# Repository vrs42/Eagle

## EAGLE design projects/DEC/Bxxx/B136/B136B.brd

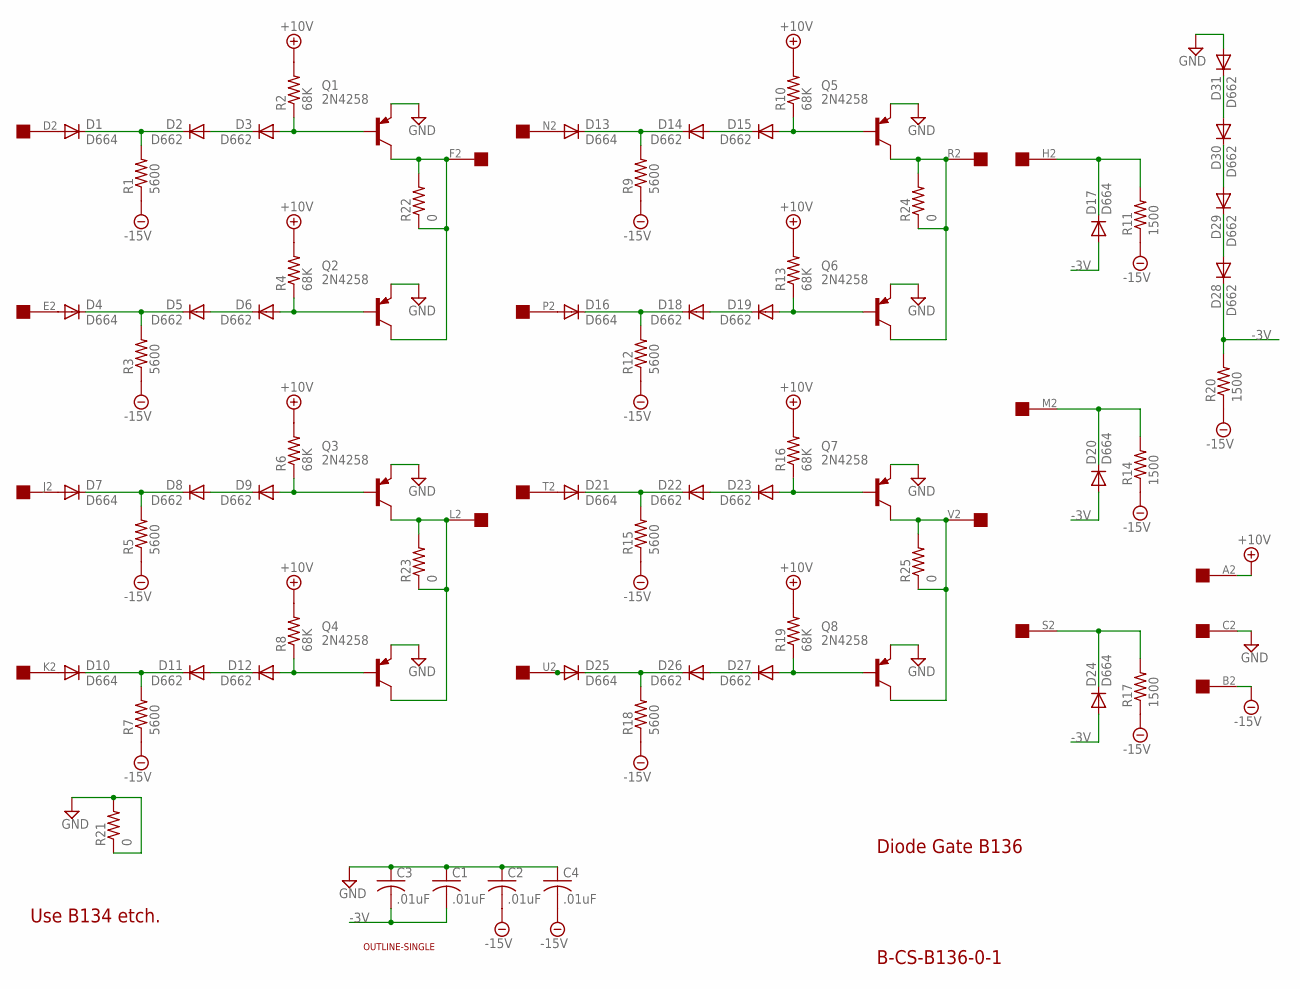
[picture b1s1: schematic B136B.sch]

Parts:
C1, C2, C3, C4: .01uF; C063-025X075
D1, D4, D7, D10, D13, D16, D17, D20, D21, D24, D25: D664; DO35-10
D2, D3, D5, D6, D8, D9, D11, D12, D14, D15, D18, D19, D22, D23, D26, D27, D28, D29, D30, D31: D662; DO35-10
Q1, Q2, Q3, Q4, Q5, Q6, Q7, Q8: 2N4258; TO5
R1, R3, R5, R7, R9, R12, R15, R18: 5600; 0207/10
R2, R4, R6, R8, R10, R13, R16, R19: 68K; 0207/10
R11, R14, R17, R20: 1500; 0207/10
R21, R22, R23, R24, R25: 0; 0207/10
U$1: OUTLINE-SINGLE; SINGLE
U$2: EDGE-1; EDGE-CON1

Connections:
+10V: R2.2, R4.2, R6.2, R8.2, R10.2, R13.2, R16.2, R19.2, U$2.A2
-3V: C1.2, C3.2, D17.A, D20.A, D24.A, D28.C, R20.2
-15V: C2.2, C4.2, R1.1, R3.1, R5.1, R7.1, R9.1, R11.1, R12.1, R14.1, R15.1, R17.1, R18.1, R20.1, U$2.B2
GND: C1.1, C2.1, C3.1, C4.1, D31.A, Q1.1 (E), Q2.1 (E), Q3.1 (E), Q4.1 (E), Q5.1 (E), Q6.1 (E), Q7.1 (E), Q8.1 (E), R21.1, R21.2, U$2.C2
unnamed: D4.C, D5.C, R3.2
unnamed: D10.C, D11.C, R7.2
unnamed: D3.A, Q1.2 (B), R2.1
unnamed: D13.C, D14.C, R9.2
unnamed: D1.C, D2.C, R1.2
unnamed: D4.A, U$2.E2
unnamed: D13.A, U$2.N2
unnamed: D11.A, D12.C
unnamed: D5.A, D6.C
unnamed: D1.A, U$2.D2
unnamed: D14.A, D15.C
unnamed: D6.A, Q2.2 (B), R4.1
unnamed: Q1.3 (C), Q2.3 (C), R22.1, R22.2, U$2.F2
unnamed: D7.C, D8.C, R5.2
unnamed: D2.A, D3.C
unnamed: D7.A, U$2.J2
unnamed: D17.C, R11.2, U$2.H2
unnamed: D15.A, Q5.2 (B), R10.1
unnamed: D10.A, U$2.K2
unnamed: D20.C, R14.2, U$2.M2
unnamed: D8.A, D9.C
unnamed: D9.A, Q3.2 (B), R6.1
unnamed: D16.C, D18.C, R12.2
unnamed: D12.A, Q4.2 (B), R8.1
unnamed: D24.C, R17.2, U$2.S2
unnamed: D30.A, D31.C
unnamed: D29.A, D30.C
unnamed: D19.A, Q6.2 (B), R13.1
unnamed: D28.A, D29.C
unnamed: D18.A, D19.C
unnamed: D23.A, Q7.2 (B), R16.1
unnamed: D21.C, D22.C, R15.2
unnamed: D22.A, D23.C
unnamed: D27.A, Q8.2 (B), R19.1
unnamed: D16.A, U$2.P2
unnamed: D21.A, U$2.T2
unnamed: D25.C, D26.C, R18.2
unnamed: D26.A, D27.C
unnamed: Q7.3 (C), Q8.3 (C), R25.1, R25.2, U$2.V2
unnamed: D25.A, U$2.U2
unnamed: Q3.3 (C), Q4.3 (C), R23.1, R23.2, U$2.L2
unnamed: Q5.3 (C), Q6.3 (C), R24.1, R24.2, U$2.R2

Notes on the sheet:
Diode Gate B136
B-CS-B136-0-1
Use B134 etch.

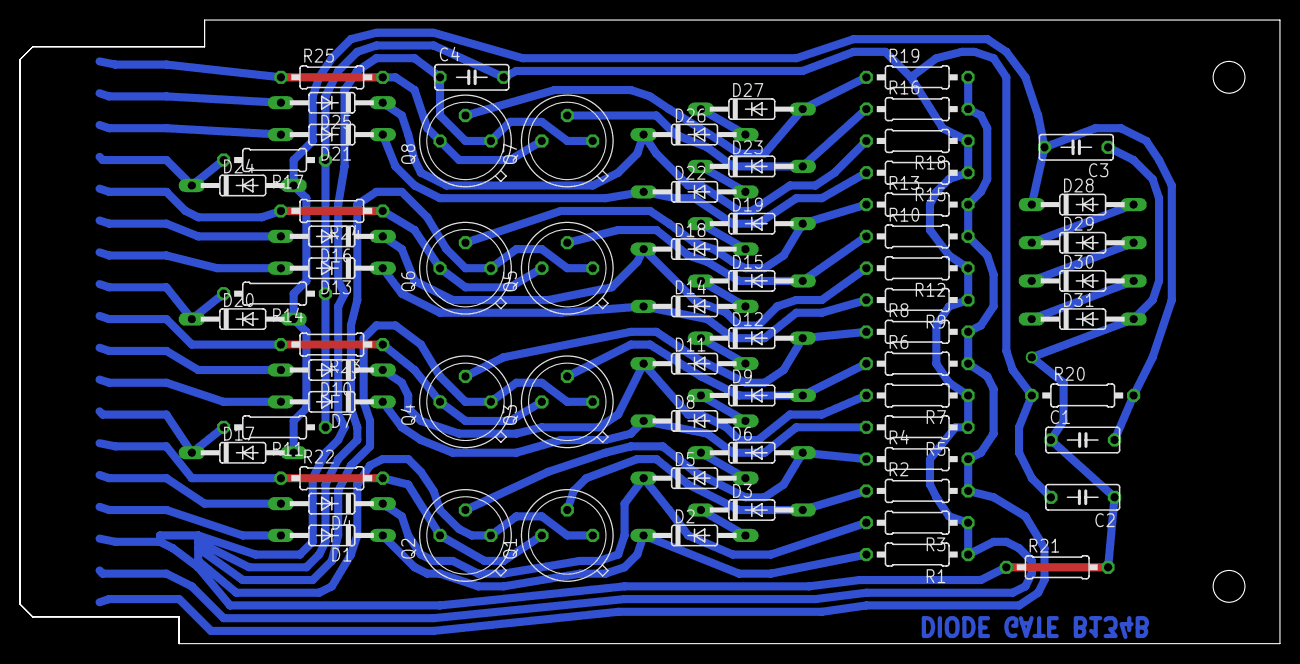
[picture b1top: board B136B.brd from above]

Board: 2 copper layers, 125.7 x 62.2 mm, 70 parts (0 on the bottom side), 46 nets.

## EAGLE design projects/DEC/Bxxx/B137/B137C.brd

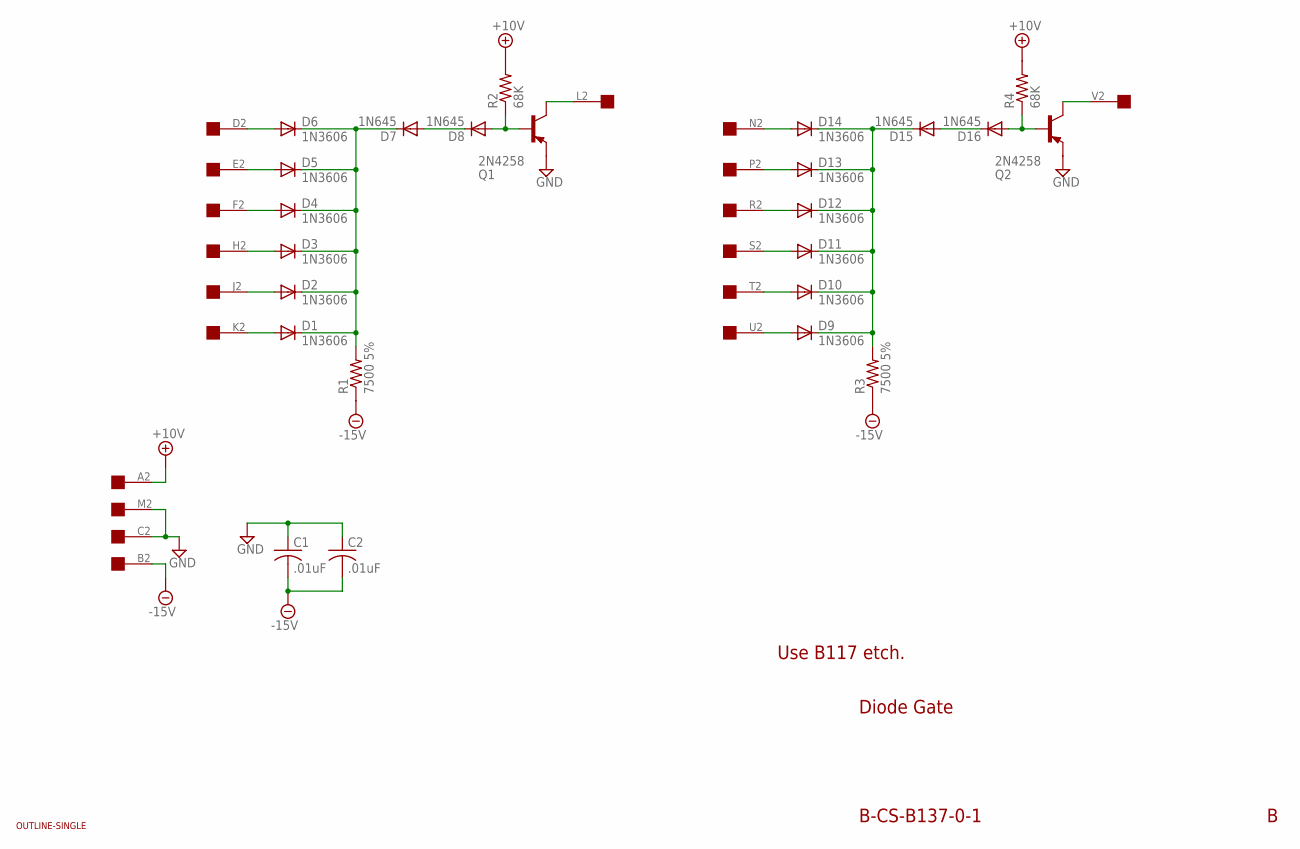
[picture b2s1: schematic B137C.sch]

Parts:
C1, C2: .01uF; C050-025X075
D1, D2, D3, D4, D5, D6, D9, D10, D11, D12, D13, D14: 1N3606; DO35-10
D7, D8, D15, D16: 1N645; DO35-10
Q1, Q2: 2N4258; TO5
R1, R3: 7500 5%; 0207/10
R2, R4: 68K; 0207/10
U$1: OUTLINE-SINGLE; SINGLE
U$2: EDGE-1; EDGE-CON1

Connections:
+10V: R2.2, R4.2, U$2.A2
-15V: C1.2, C2.2, R1.1, R3.1, U$2.B2
D: D6.A, U$2.D2
E: D5.A, U$2.E2
F: D4.A, U$2.F2
GND: C1.1, C2.1, Q1.1 (E), Q2.1 (E), U$2.C2, U$2.M2
H: D3.A, U$2.H2
J: D2.A, U$2.J2
K: D1.A, U$2.K2
L: Q1.3 (C), U$2.L2
N: D14.A, U$2.N2
unnamed: D1.C, D2.C, D3.C, D4.C, D5.C, D6.C, D7.C, R1.2
unnamed: D7.A, D8.C
unnamed: D8.A, Q1.2 (B), R2.1
unnamed: D9.C, D10.C, D11.C, D12.C, D13.C, D14.C, D15.C, R3.2
unnamed: D15.A, D16.C
unnamed: D16.A, Q2.2 (B), R4.1
P: D13.A, U$2.P2
R: D12.A, U$2.R2
S: D11.A, U$2.S2
T: D10.A, U$2.T2
U: D9.A, U$2.U2
V: Q2.3 (C), U$2.V2

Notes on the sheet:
Diode Gate
B-CS-B137-0-1
Use B117 etch.

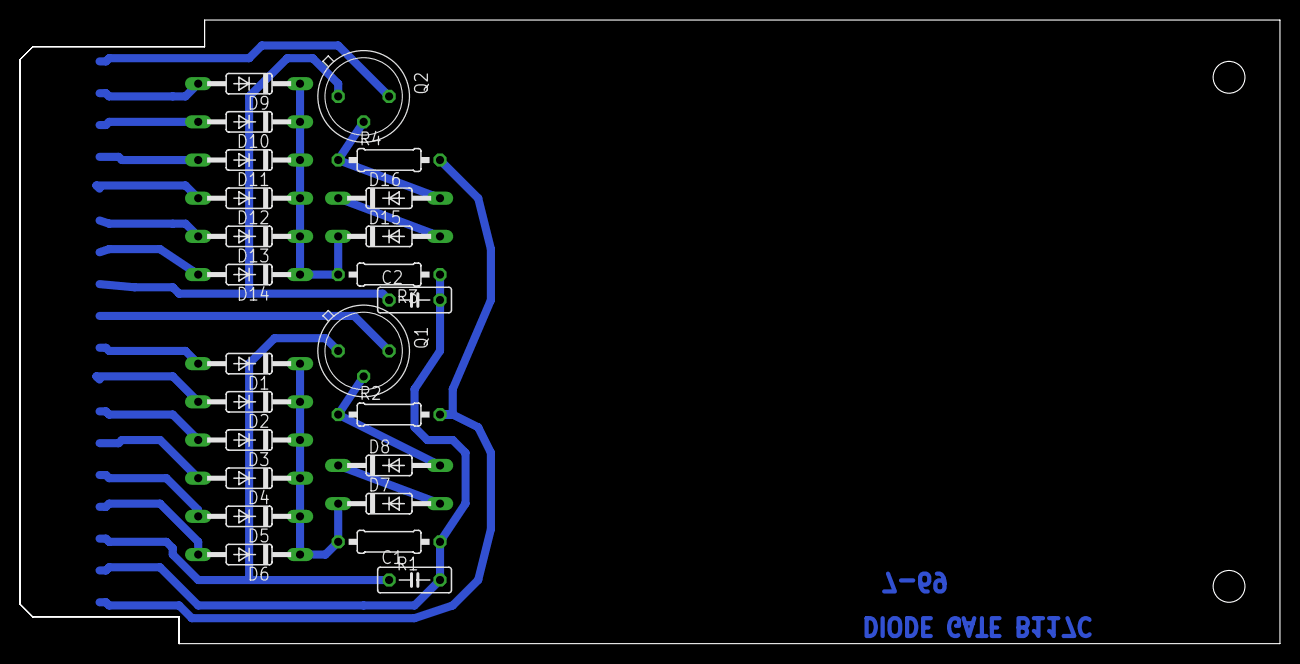
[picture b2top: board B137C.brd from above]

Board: 2 copper layers, 125.7 x 62.2 mm, 26 parts (0 on the bottom side), 23 nets.

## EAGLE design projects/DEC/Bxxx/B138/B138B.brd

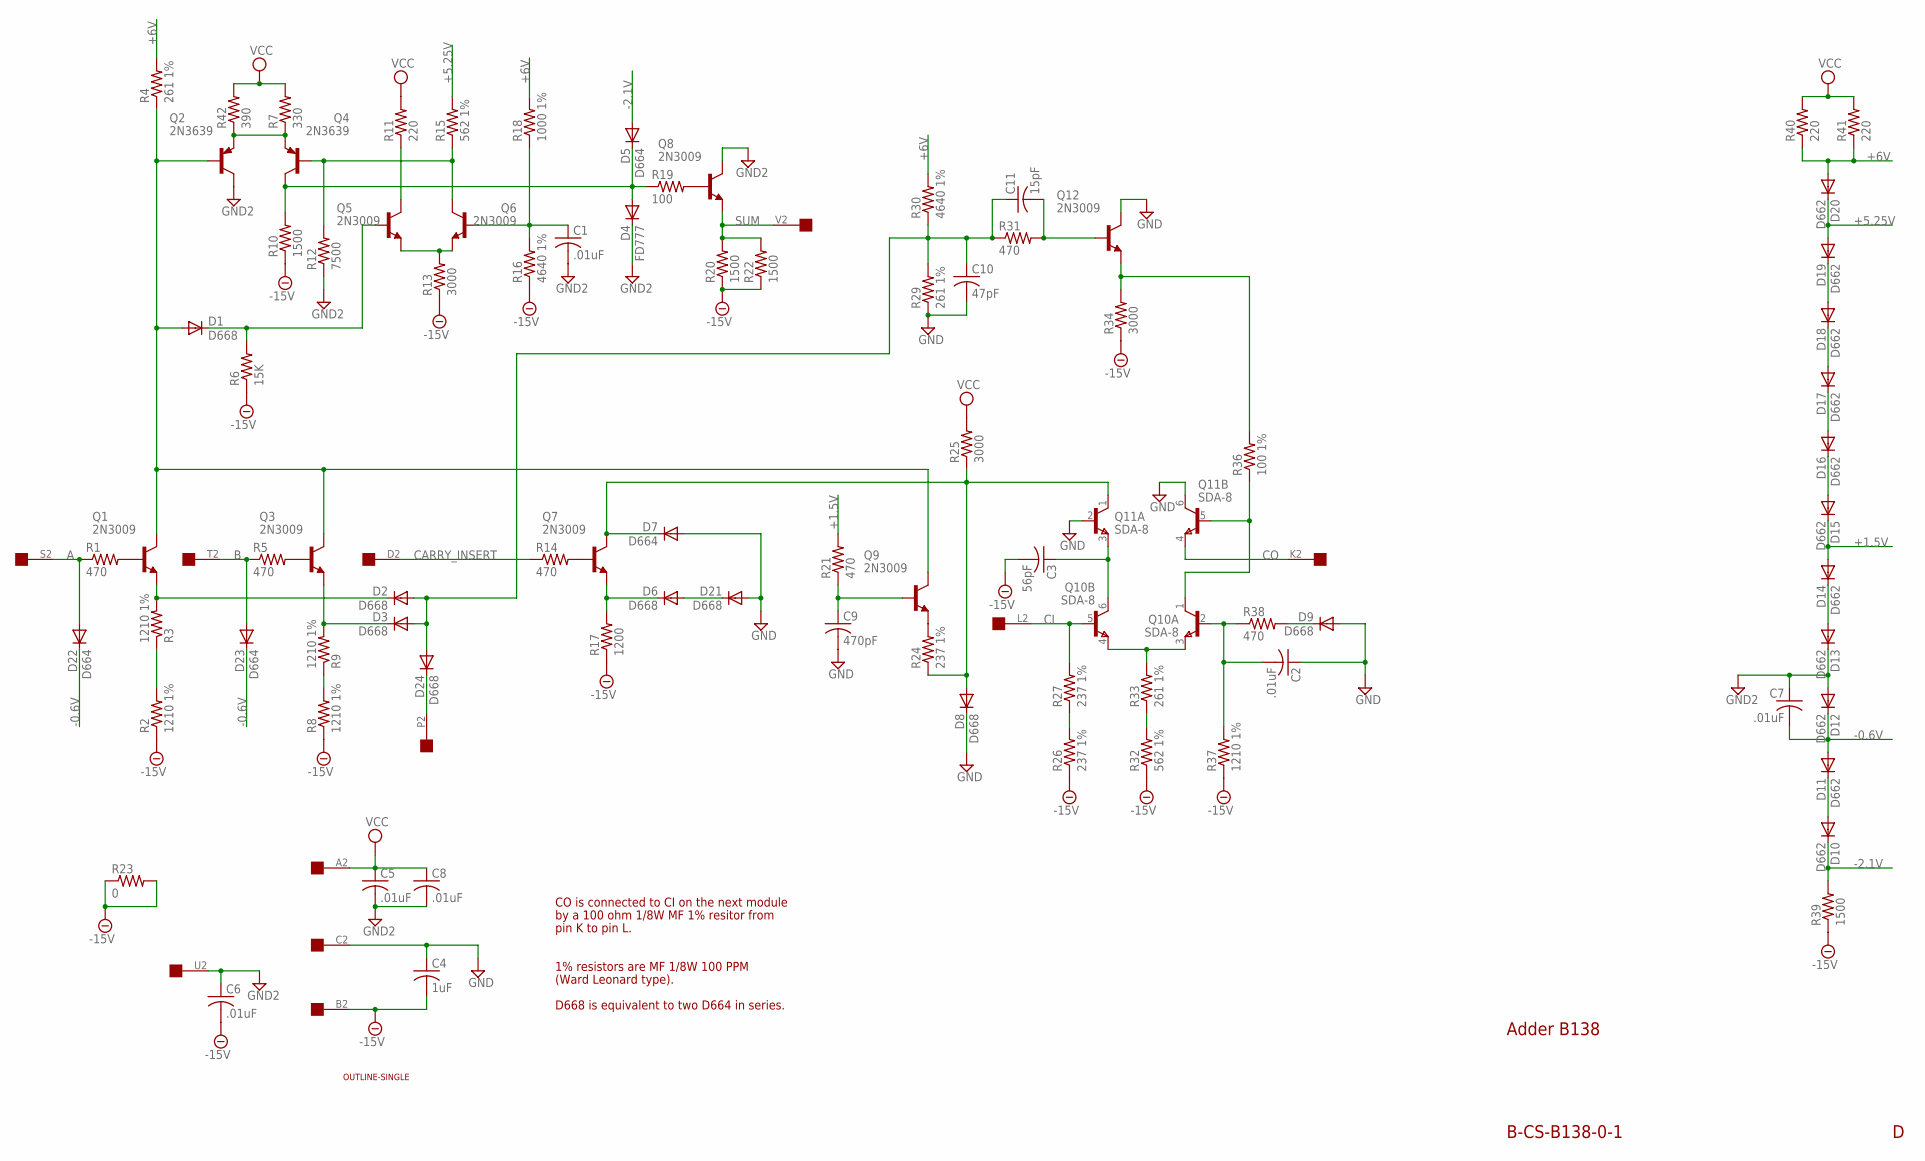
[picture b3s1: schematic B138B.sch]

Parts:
C1, C2, C5, C6, C7, C8: .01uF; C063-025X075
C3: 56pF; C063-025X075
C4: 1uF; C102-043X133
C9: 470pF; C063-025X075
C10: 47pF; C063-025X075
C11: 15pF; C063-025X075
D1, D2, D3, D6, D8, D9, D21, D24: D668; DO35-10
D4: FD777; DO35-10
D5, D7, D22, D23: D664; DO35-10
D10, D11, D12, D13, D14, D15, D16, D17, D18, D19, D20: D662; DO35-10
Q1, Q3, Q5, Q6, Q7, Q8, Q9, Q12: 2N3009; TO5
Q2, Q4: 2N3639; TO5
Q10, Q11: SDA-8; TO78
R1, R5, R14, R21, R31, R38: 470; 0207/10
R2, R3, R8, R9, R37: 1210 1%; 0207/15
R4, R29, R33: 261 1%; 0207/15
R6: 15K; 0207/10
R7: 330; 0207/10
R10, R20, R22, R39: 1500; 0207/10
R11, R40, R41: 220; 0207/10
R12: 7500; 0207/10
R13, R25, R34: 3000; 0207/10
R15, R32: 562 1%; 0207/15
R16, R30: 4640 1%; 0207/15
R17: 1200; 0207/10
R18: 1000 1%; 0207/15
R19: 100; 0207/10
R23: 0; 0207/10
R24, R26, R27: 237 1%; 0207/15
R36: 100 1%; 0207/15
R42: 390; 0207/10
U$1: OUTLINE-SINGLE; SINGLE
U$2: EDGE-1; EDGE-CON1

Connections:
+1.5V: D14.A, D15.C, R21.2
+5.25V: D19.A, D20.C, R15.2
+6V: D20.A, R4.2, R18.2, R30.2, R40.1, R41.1
-0.6V: C7.2, D11.A, D12.C, D22.C, D23.C
-2.1V: D5.A, D10.C, R39.2
-15V: C3.2, C4.2, C6.2, R2.1, R6.1, R8.1, R10.1, R13.1, R16.1, R17.1, R20.1, R22.1, R23.1, R23.2, R26.1, R32.1, R34.1, R37.1, R39.1, U$2.B2
A: D22.A, R1.1, U$2.S2
B: D23.A, R5.1, U$2.T2
CARRY_INSERT: R14.1, U$2.D2
CI: Q10.5 (B), R27.2, U$2.L2
CO: Q11.4 (E), U$2.K2
GND: C2.1, C4.1, C9.2, C10.2, D7.A, D8.C, D9.A, D21.A, Q11.2 (B), Q11.6 (C), Q12.3 (C), R29.1, U$2.C2
GND2: C1.2, C5.2, C6.1, C7.1, C8.2, D4.C, D12.A, D13.C, Q2.3 (C), Q8.3 (C), R12.1, U$2.U2
unnamed: D1.A, Q1.3 (C), Q2.2 (B), Q3.3 (C), Q9.3 (C), R4.1
unnamed: D2.C, Q1.1 (E), R3.2
unnamed: R2.2, R3.1
unnamed: D3.C, Q3.1 (E), R9.2
unnamed: R8.2, R9.1
unnamed: Q1.2 (B), R1.2
unnamed: Q3.2 (B), R5.2
unnamed: D24.C, U$2.P2
unnamed: C10.1, C11.1, D2.A, D3.A, D24.A, R29.2, R30.1, R31.1
unnamed: D6.C, Q7.1 (E), R17.2
unnamed: Q7.2 (B), R14.2
unnamed: D6.A, D21.C
unnamed: D7.C, D8.A, Q7.3 (C), Q11.1 (C), R24.1, R25.1
unnamed: Q9.1 (E), R24.2
unnamed: C9.1, Q9.2 (B), R21.1
unnamed: Q10.3 (E), Q10.4 (E), R33.2
unnamed: R32.2, R33.1
unnamed: D17.A, D18.C
unnamed: D18.A, D19.C
unnamed: C3.1, Q10.6 (C), Q11.3 (E)
unnamed: D15.A, D16.C
unnamed: D16.A, D17.C
unnamed: D13.A, D14.C
unnamed: Q10.1 (C), Q11.5 (B), R36.1
unnamed: R26.2, R27.1
unnamed: D10.A, D11.C
unnamed: C2.2, Q10.2 (B), R37.2, R38.1
unnamed: D9.C, R38.2
unnamed: Q2.1 (E), Q4.1 (E), R7.1, R42.1
unnamed: C1.1, Q6.2 (B), R16.2, R18.1
unnamed: Q5.1 (E), Q6.1 (E), R13.2
unnamed: Q5.3 (C), R11.1
unnamed: Q4.2 (B), Q6.3 (C), R12.2, R15.1
unnamed: D4.A, D5.C, Q4.3 (C), R10.2, R19.1
unnamed: D1.C, Q5.2 (B), R6.2
unnamed: Q8.2 (B), R19.2
unnamed: C11.2, Q12.2 (B), R31.2
unnamed: Q12.1 (E), R34.2, R36.2
SUM: Q8.1 (E), R20.2, R22.2, U$2.V2
VCC: C5.1, C8.1, R7.2, R11.2, R25.2, R40.2, R41.2, R42.2, U$2.A2

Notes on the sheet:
Adder B138
B-CS-B138-0-1
CO is connected to CI on the next module
by a 100 ohm 1/8W MF 1% resitor from
pin K to pin L.
1% resistors are MF 1/8W 100 PPM
(Ward Leonard type).
D668 is equivalent to two D664 in series.

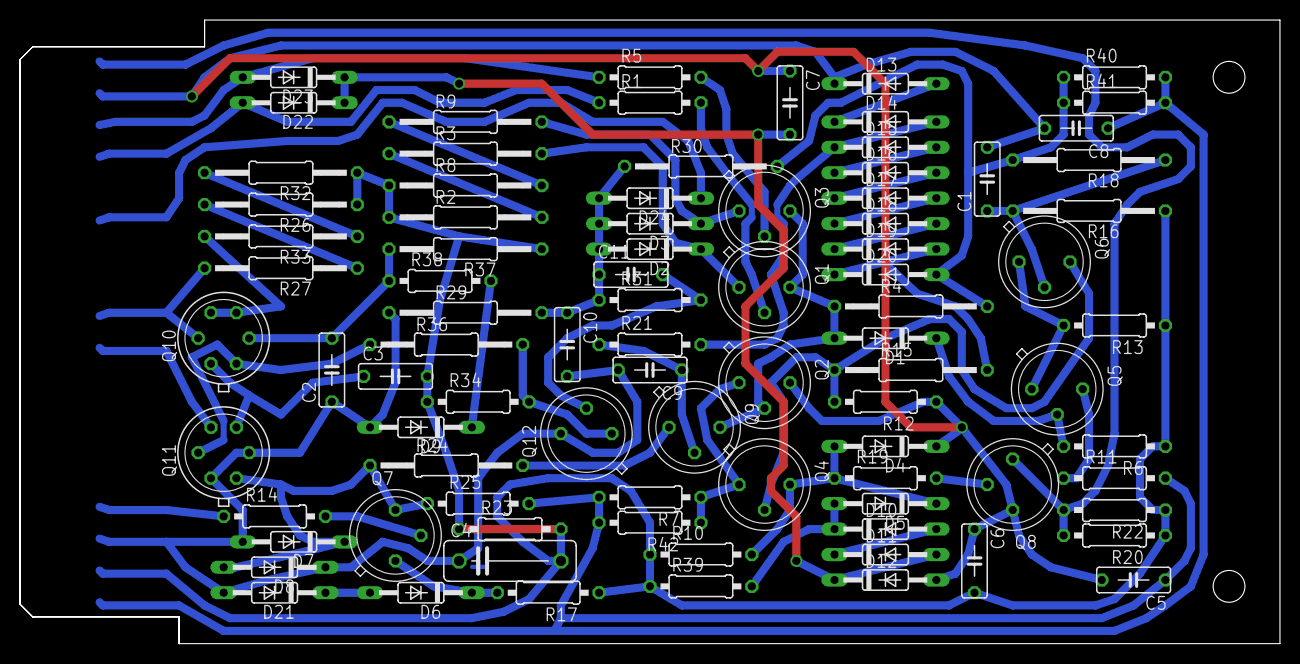
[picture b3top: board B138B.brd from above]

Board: 2 copper layers, 125.7 x 62.2 mm, 89 parts (0 on the bottom side), 53 nets.

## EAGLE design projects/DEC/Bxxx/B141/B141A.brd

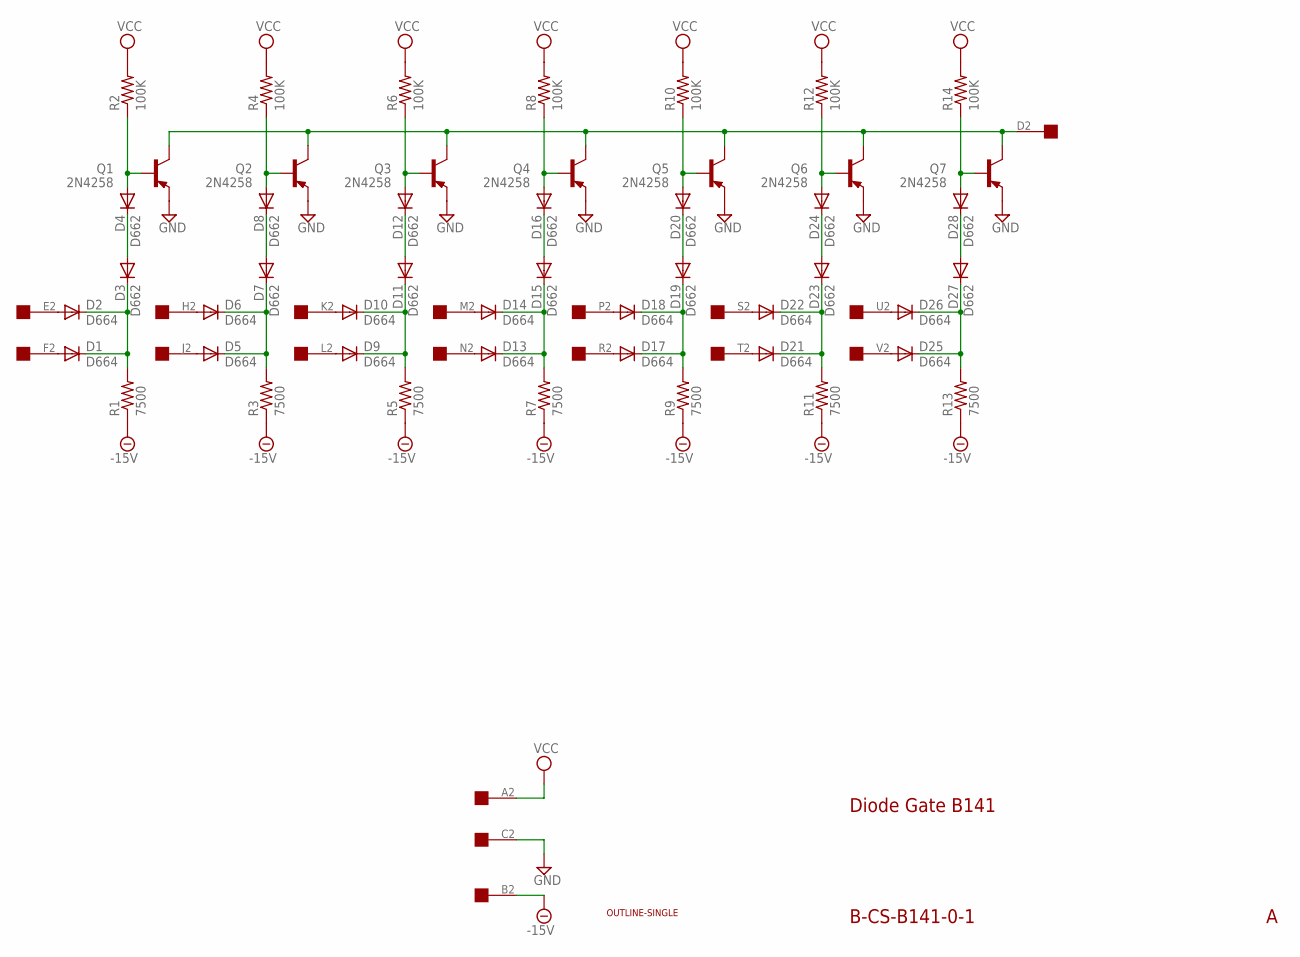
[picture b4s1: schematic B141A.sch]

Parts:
D1, D2, D5, D6, D9, D10, D13, D14, D17, D18, D21, D22, D25, D26: D664; DO35-10
D3, D4, D7, D8, D11, D12, D15, D16, D19, D20, D23, D24, D27, D28: D662; DO35-10
Q1, Q2, Q3, Q4, Q5, Q6, Q7: 2N4258; TO5
R1, R3, R5, R7, R9, R11, R13: 7500; 0207/10
R2, R4, R6, R8, R10, R12, R14: 100K; 0207/10
U$1: OUTLINE-SINGLE; SINGLE
U$2: EDGE-1; EDGE-CON1

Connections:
-15V: R1.1, R3.1, R5.1, R7.1, R9.1, R11.1, R13.1, U$2.B2
GND: Q1.1 (E), Q2.1 (E), Q3.1 (E), Q4.1 (E), Q5.1 (E), Q6.1 (E), Q7.1 (E), U$2.C2
unnamed: D2.A, U$2.E2
unnamed: D1.C, D2.C, D3.C, R1.2
unnamed: D3.A, D4.C
unnamed: D1.A, U$2.F2
unnamed: D4.A, Q1.2 (B), R2.1
unnamed: Q1.3 (C), Q2.3 (C), Q3.3 (C), Q4.3 (C), Q5.3 (C), Q6.3 (C), Q7.3 (C), U$2.D2
unnamed: D5.C, D6.C, D7.C, R3.2
unnamed: D7.A, D8.C
unnamed: D8.A, Q2.2 (B), R4.1
unnamed: D6.A, U$2.H2
unnamed: D9.C, D10.C, D11.C, R5.2
unnamed: D11.A, D12.C
unnamed: D12.A, Q3.2 (B), R6.1
unnamed: D10.A, U$2.K2
unnamed: D13.C, D14.C, D15.C, R7.2
unnamed: D15.A, D16.C
unnamed: D16.A, Q4.2 (B), R8.1
unnamed: D9.A, U$2.L2
unnamed: D14.A, U$2.M2
unnamed: D17.C, D18.C, D19.C, R9.2
unnamed: D19.A, D20.C
unnamed: D13.A, U$2.N2
unnamed: D20.A, Q5.2 (B), R10.1
unnamed: D18.A, U$2.P2
unnamed: D21.C, D22.C, D23.C, R11.2
unnamed: D23.A, D24.C
unnamed: D24.A, Q6.2 (B), R12.1
unnamed: D17.A, U$2.R2
unnamed: D25.C, D26.C, D27.C, R13.2
unnamed: D27.A, D28.C
unnamed: D28.A, Q7.2 (B), R14.1
unnamed: D22.A, U$2.S2
unnamed: D5.A, U$2.J2
unnamed: D21.A, U$2.T2
unnamed: D26.A, U$2.U2
unnamed: D25.A, U$2.V2
VCC: R2.2, R4.2, R6.2, R8.2, R10.2, R12.2, R14.2, U$2.A2

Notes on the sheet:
B-CS-B141-0-1
Diode Gate B141

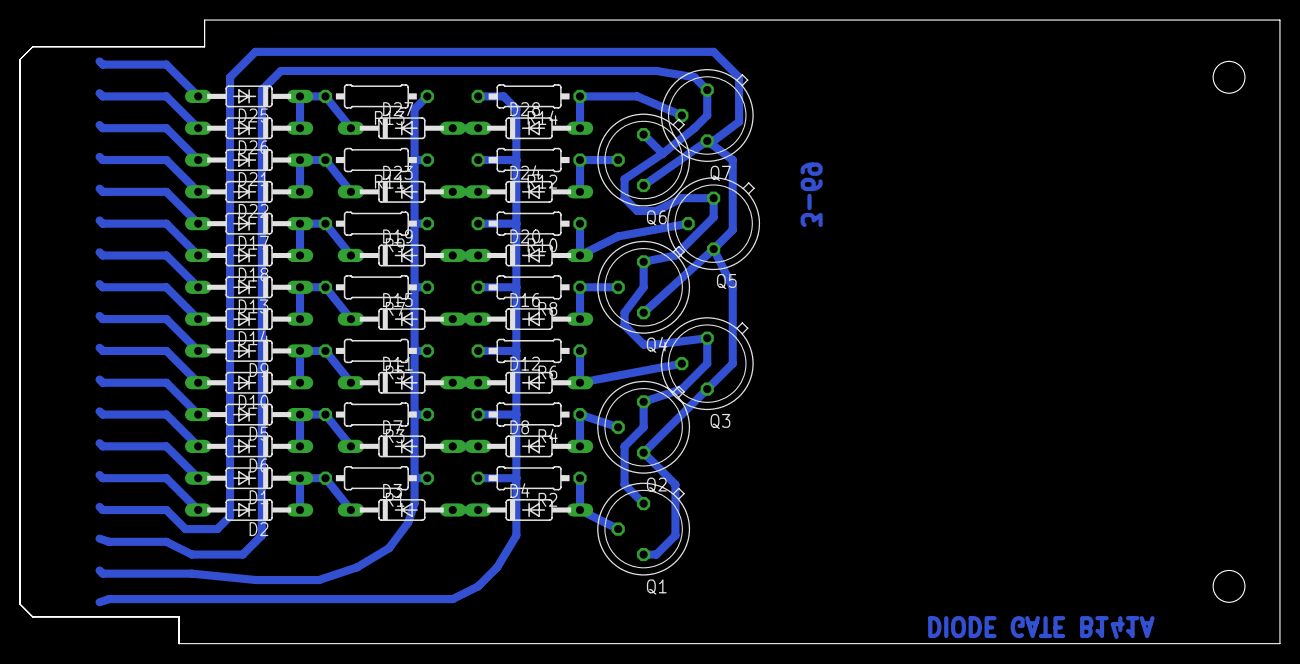
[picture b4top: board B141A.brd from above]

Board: 2 copper layers, 125.7 x 62.2 mm, 51 parts (0 on the bottom side), 39 nets.
